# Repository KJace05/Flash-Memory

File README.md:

# Flash Memory

> An Arduino-based memory game inspired by Simon Says — built with C++ for the Arduino Uno.

## About

Flash Memory challenges players to watch a randomly generated sequence of colored LED flashes and recreate it by pressing the matching colored buttons in the correct order. The sequence grows longer with each level, testing both memory and focus.

A buzzer sounds with every LED flash during the sequence display, giving players an audio cue to count flashes by ear alongside the visual pattern.

---

##  Gameplay

1. **Watch** — colored LEDs flash a random sequence with an accompanying buzzer beep per flash
2. **Repeat** — press the matching colored buttons in the same order
3. **Progress** — complete the sequence correctly to advance to the next level
4. **Win** — complete all 5 levels

### Wrong Guess
- All 4 colored LEDs flash simultaneously
- Buzzer sounds to signal the incorrect answer
- A short delay prevents further input
- The same sequence replays automatically — unlimited attempts per level

### Replay Button
Forgot the sequence mid-guess? Press the dedicated replay button at any time during the input phase to rewatch the same sequence without generating a new one.

---

##  Levels

| Level | Sequence Length | Progress LED |
|-------|----------------|-------------|
| 1 | 2 flashes | ⚪ |
| 2 | 3 flashes | ⚪⚪ |
| 3 | 4 flashes | ⚪⚪⚪ |
| 4 | 5 flashes | ⚪⚪⚪⚪ |
| 5 | 6 flashes | ⚪⚪⚪⚪⚪ |

Five white LEDs connected to a 74HC595 shift register light up one by one as each level is completed, giving a persistent visual indicator of progress.

---

## Randomization

Every game generates a unique sequence using the Arduino `EEPROM` library as a persistent seed generator. On each power cycle, the stored seed is read, incremented, and written back, ensuring a different sequence every playthrough, even across power cycles.

---

## Hardware

| Component | Quantity | Notes |
|-----------|----------|-------|
| Arduino Uno | 1 | Microcontroller |
| Colored LEDs | 4 | Red, Green, Yellow, Blue |
| Colored buttons | 4 | Matching colors |
| White LEDs | 5 | Level progress indicator |
| 74HC595 shift register | 1 | Drives white LEDs + buzzer |
| Active buzzer | 1 | Connected to Q0 on shift register |
| 16x2 LCD display | 1 | Shows title and game state |
| Replay button | 1 | Replays current sequence |
| Resistors | Various | Current limiting for LEDs |
| Potentiometer | 1 | Controls LCD brightness

---

##  Pin Map

| Pin | Assignment |
|-----|-----------|
| `2` | LCD D7 |
| `3` | Blue button |
| `4` | Yellow button |
| `5` | Green button |
| `6` | Red button |
| `7` | 74HC595 Clock |
| `8` | 74HC595 Latch |
| `9` | 74HC595 Data |
| `10` | Red LED |
| `11` | Green LED |
| `12` | Yellow LED |
| `13` | Blue LED |
| `A0` | LCD RS |
| `A1` | LCD Enable |
| `A2` | LCD D4 |
| `A3` | LCD D5 |
| `A4` | LCD D6 |
| `A5` | Replay button |

### 74HC595 Output Map
| Bit | Assignment |
|-----|-----------|
| Q0 | Buzzer |
| Q1–Q5 | White LEDs 1–5 |
| Q6–Q7 | Unused |

---

## Libraries

```cpp
#include <LiquidCrystal.h>   // LCD display control
#include <EEPROM.h>           // Persistent seed storage for randomization
```

---

## Technical Notes

- Sequence timing uses **`millis()`** for non-blocking LED flashing — the Arduino remains responsive during the display phase
- **`delay()`** is used selectively to gate player input at key moments (wrong guess lockout, level transition pause)
- The buzzer and white LEDs share the same 74HC595 — all shift register writes preserve the full byte state to prevent unintentional outputs
- `EEPROM.get()` / `EEPROM.put()` store a 4-byte `unsigned long` seed (0 to ~4 billion) for maximum sequence variety

---

## Getting Started

1. Wire components according to the pin map above
2. Install the Arduino IDE
3. Open `FlashMemory.ino`
4. Select **Arduino Uno** as the board
5. Upload and play

---

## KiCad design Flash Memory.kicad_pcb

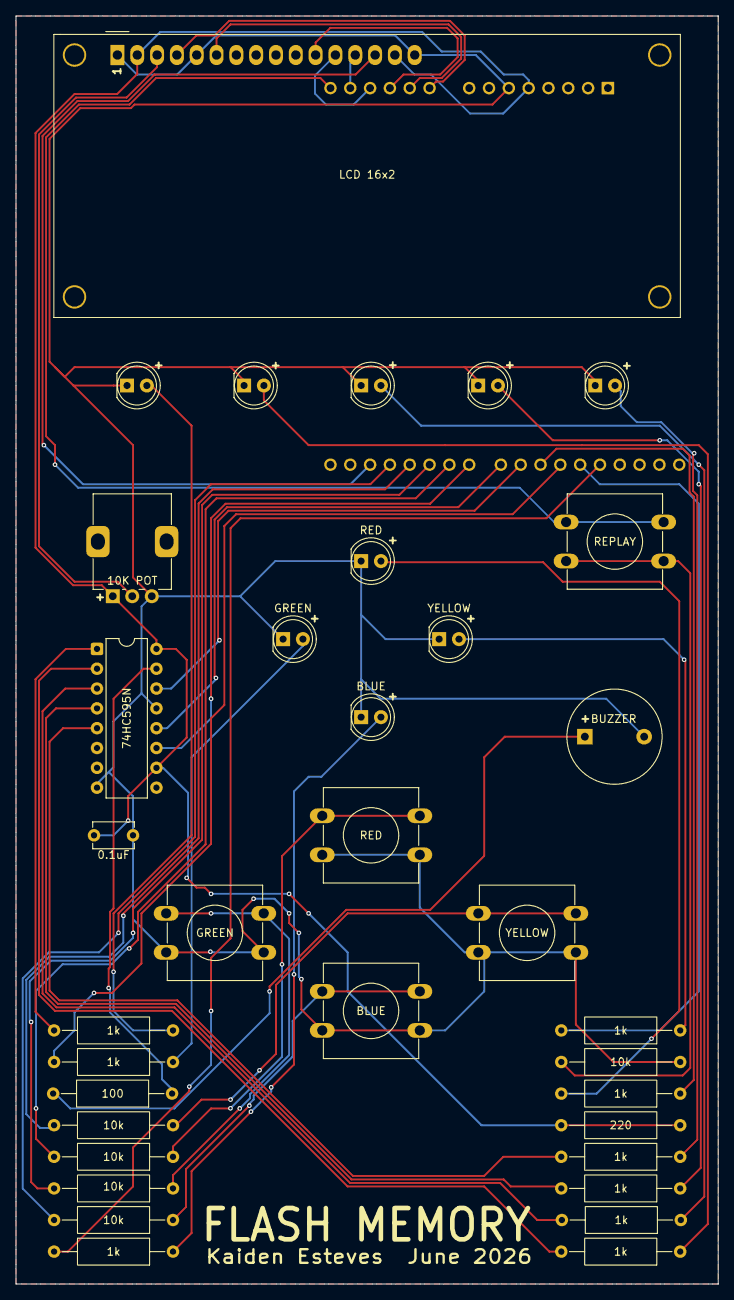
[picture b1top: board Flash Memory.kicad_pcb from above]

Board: 2 copper layers, 90.0 x 162.5 mm, 36 parts (1 on the bottom side), 42 nets.

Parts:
74HC595N: 74HC595; DIP-16_W7.62mm
Arduino1: Arduino_UNO_R3
BLUE: LED; LED_D5.0mm
BUZZER: Buzzer; Buzzer_12x9.5RM7.6
Button_B1: SW_Push; SW_PUSH-12mm
Button_G1: SW_Push; SW_PUSH-12mm
Button_R1: SW_Push; SW_PUSH-12mm
Button_Y1: SW_Push; SW_PUSH-12mm
C1: .1uf; C_Disc_D5.1mm_W3.2mm_P5.00mm
GREEN: LED; LED_D5.0mm
LCD 16x2: WC1602A
Level_1, Level_2, Level_3, Level_4, Level_5: LED; LED_D5.0mm
Potentiometer1: R_Potentiometer; Potentiometer_Alps_RK09K_Single_Vertical
RED: LED; LED_D5.0mm
REPLAY: SW_Push; SW_PUSH-12mm
YELLOW: LED; LED_D5.0mm
r_blue1: 1k; R_Axial_DIN0309_L9.0mm_D3.2mm_P15.24mm_Horizontal
r_butt_blue1: 10k; R_Axial_DIN0309_L9.0mm_D3.2mm_P15.24mm_Horizontal
r_butt_green1: 10k; R_Axial_DIN0309_L9.0mm_D3.2mm_P15.24mm_Horizontal
r_butt_red1: 10k; R_Axial_DIN0309_L9.0mm_D3.2mm_P15.24mm_Horizontal
r_butt_yellow1: 10k; R_Axial_DIN0309_L9.0mm_D3.2mm_P15.24mm_Horizontal
r_buzz1: 100; R_Axial_DIN0309_L9.0mm_D3.2mm_P15.24mm_Horizontal
r_green1: 1k; R_Axial_DIN0309_L9.0mm_D3.2mm_P15.24mm_Horizontal
r_l1, r_l2, r_l3, r_l4, r_l5: 1k; R_Axial_DIN0309_L9.0mm_D3.2mm_P15.24mm_Horizontal
r_pot1: 220; R_Axial_DIN0309_L9.0mm_D3.2mm_P15.24mm_Horizontal
r_red1: 1k; R_Axial_DIN0309_L9.0mm_D3.2mm_P15.24mm_Horizontal
r_replay1: 10k; R_Axial_DIN0309_L9.0mm_D3.2mm_P15.24mm_Horizontal
r_yellow1: 1k; R_Axial_DIN0309_L9.0mm_D3.2mm_P15.24mm_Horizontal

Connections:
+5V: 74HC595N.10 (~SRCLR), 74HC595N.16 (VCC), Arduino1.5 (+5V), C1.1, LCD 16x2.2 (VDD), LCD 16x2.15 (LED(+)), Potentiometer1.1, r_pot1.1, r_pot1.2
GND: 74HC595N.8 (GND), 74HC595N.13 (~OE), Arduino1.6 (GND), BLUE.1 (K), BUZZER.2 (-), Button_B1.2, Button_G1.2, Button_R1.2, Button_Y1.2, C1.2, GREEN.1 (K), LCD 16x2.1 (VSS), LCD 16x2.5 (R/W), LCD 16x2.16 (LED(-)), Level_1.1 (K), Level_2.1 (K), Level_3.1 (K), Level_4.1 (K), Level_5.1 (K), Potentiometer1.3, RED.1 (K), YELLOW.1 (K), r_replay1.1
unnamed: Arduino1.9 (A0), LCD 16x2.4 (RS)
unnamed: Arduino1.10 (A1), LCD 16x2.6 (E)
unnamed: Arduino1.11 (A2), LCD 16x2.11 (D4)
unnamed: Arduino1.12 (A3), LCD 16x2.12 (D5)
unnamed: Arduino1.17 (D2), LCD 16x2.14 (D7)
unnamed: Arduino1.18 (D3), r_butt_blue1.2
unnamed: Arduino1.19 (D4), r_butt_yellow1.2
unnamed: Arduino1.20 (D5), r_butt_green1.2
unnamed: Arduino1.21 (D6), r_butt_red1.2
unnamed: 74HC595N.11 (SRCLK), Arduino1.22 (D7)
unnamed: 74HC595N.12 (RCLK), Arduino1.23 (D8)
unnamed: 74HC595N.14 (SER), Arduino1.24 (D9)
unnamed: Arduino1.25 (D10), r_red1.1
unnamed: Arduino1.26 (D11), r_green1.2
unnamed: Arduino1.27 (D12), r_yellow1.2
unnamed: Arduino1.28 (D13), r_blue1.2
unnamed: Arduino1.14 (SCL/A5), REPLAY.1
unnamed: BUZZER.1 (+), r_buzz1.2
unnamed: BLUE.2 (A), r_blue1.1
unnamed: Button_B1.1, r_butt_blue1.1
unnamed: Button_G1.1, r_butt_green1.1
unnamed: Button_R1.1, r_butt_red1.1
unnamed: Button_Y1.1, r_butt_yellow1.1
unnamed: GREEN.2 (A), r_green1.1
unnamed: 74HC595N.15 (QA), r_buzz1.1
unnamed: 74HC595N.1 (QB), r_l1.2
unnamed: 74HC595N.2 (QC), r_l2.2
unnamed: 74HC595N.3 (QD), r_l3.2
unnamed: 74HC595N.4 (QE), r_l4.2
unnamed: 74HC595N.5 (QF), r_l5.2
unnamed: Arduino1.13 (SDA/A4), LCD 16x2.13 (D6)
unnamed: LCD 16x2.3 (VO), Potentiometer1.2
unnamed: Level_1.2 (A), r_l1.1
unnamed: Level_2.2 (A), r_l2.1
unnamed: Level_3.2 (A), r_l3.1
unnamed: Level_4.2 (A), r_l4.1
unnamed: Level_5.2 (A), r_l5.1
unnamed: RED.2 (A), r_red1.2
unnamed: REPLAY.2, r_replay1.2
unnamed: YELLOW.2 (A), r_yellow1.1
